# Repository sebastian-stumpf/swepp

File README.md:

# swepp

## Attention

I'm a hobbyist/amateur at best. So there may be things that aren't optimized. That being said I've had the files
in the `gerbers/` directory manufactured at JLC with 1.6mm thickness and they work just fine with my fork of the qmk repository
directory. So if you decide to use this, then please be advised that I'm not providing any sort of liability and you should
exercise some caution.

## Case

There are three options for the case: The first one is a simple FR4 stack. You'll need some M2 spacers and screws to fix it all
together. Plates and bottoms are reversible. The second option is a simple tray case. You'll need M2 heat inserts and screws to
fix the plate to the bottom. If you don't like the 3d printed plate you can also use the FR4 plate with spacers in this case.
The final option is a massive gasket mounted case that hides the switches.

## BOM

| Quantity   | Item                               | Comment                       |
| ---------  | ---------------------------------- | ----------------------------- |
| 2          | Helios or Liatris Controller       |                               |
| 2          | IC-Sockets+Pins for MCU            | Optional but recommended      |
| 2          | TRRS Sockets                       |                               |
| 2          | SKHLLBA010 buttons                 |                               |
| 34         | MX Hotswap Sockets                 |                               |
| 34         | MX Switches + Keycaps              |                               |
| 12         | M2 Screws                          | (countersunk for gasket case) |
| 12         | M2 heat inserts                    | Only for the 3d printed cases |

## Firmware

See [my fork](https://github.com/sebastian-stumpf/qmk_firmware/tree/sepp/keyboards/swepp) of the qmk repository. Nothing special here.
You can just copy the code over to your own repository and adjust the keymap.

## Feedback

I'm always happy to hear your opinions about this and if you decide to build this board then please do send me a picture of it.

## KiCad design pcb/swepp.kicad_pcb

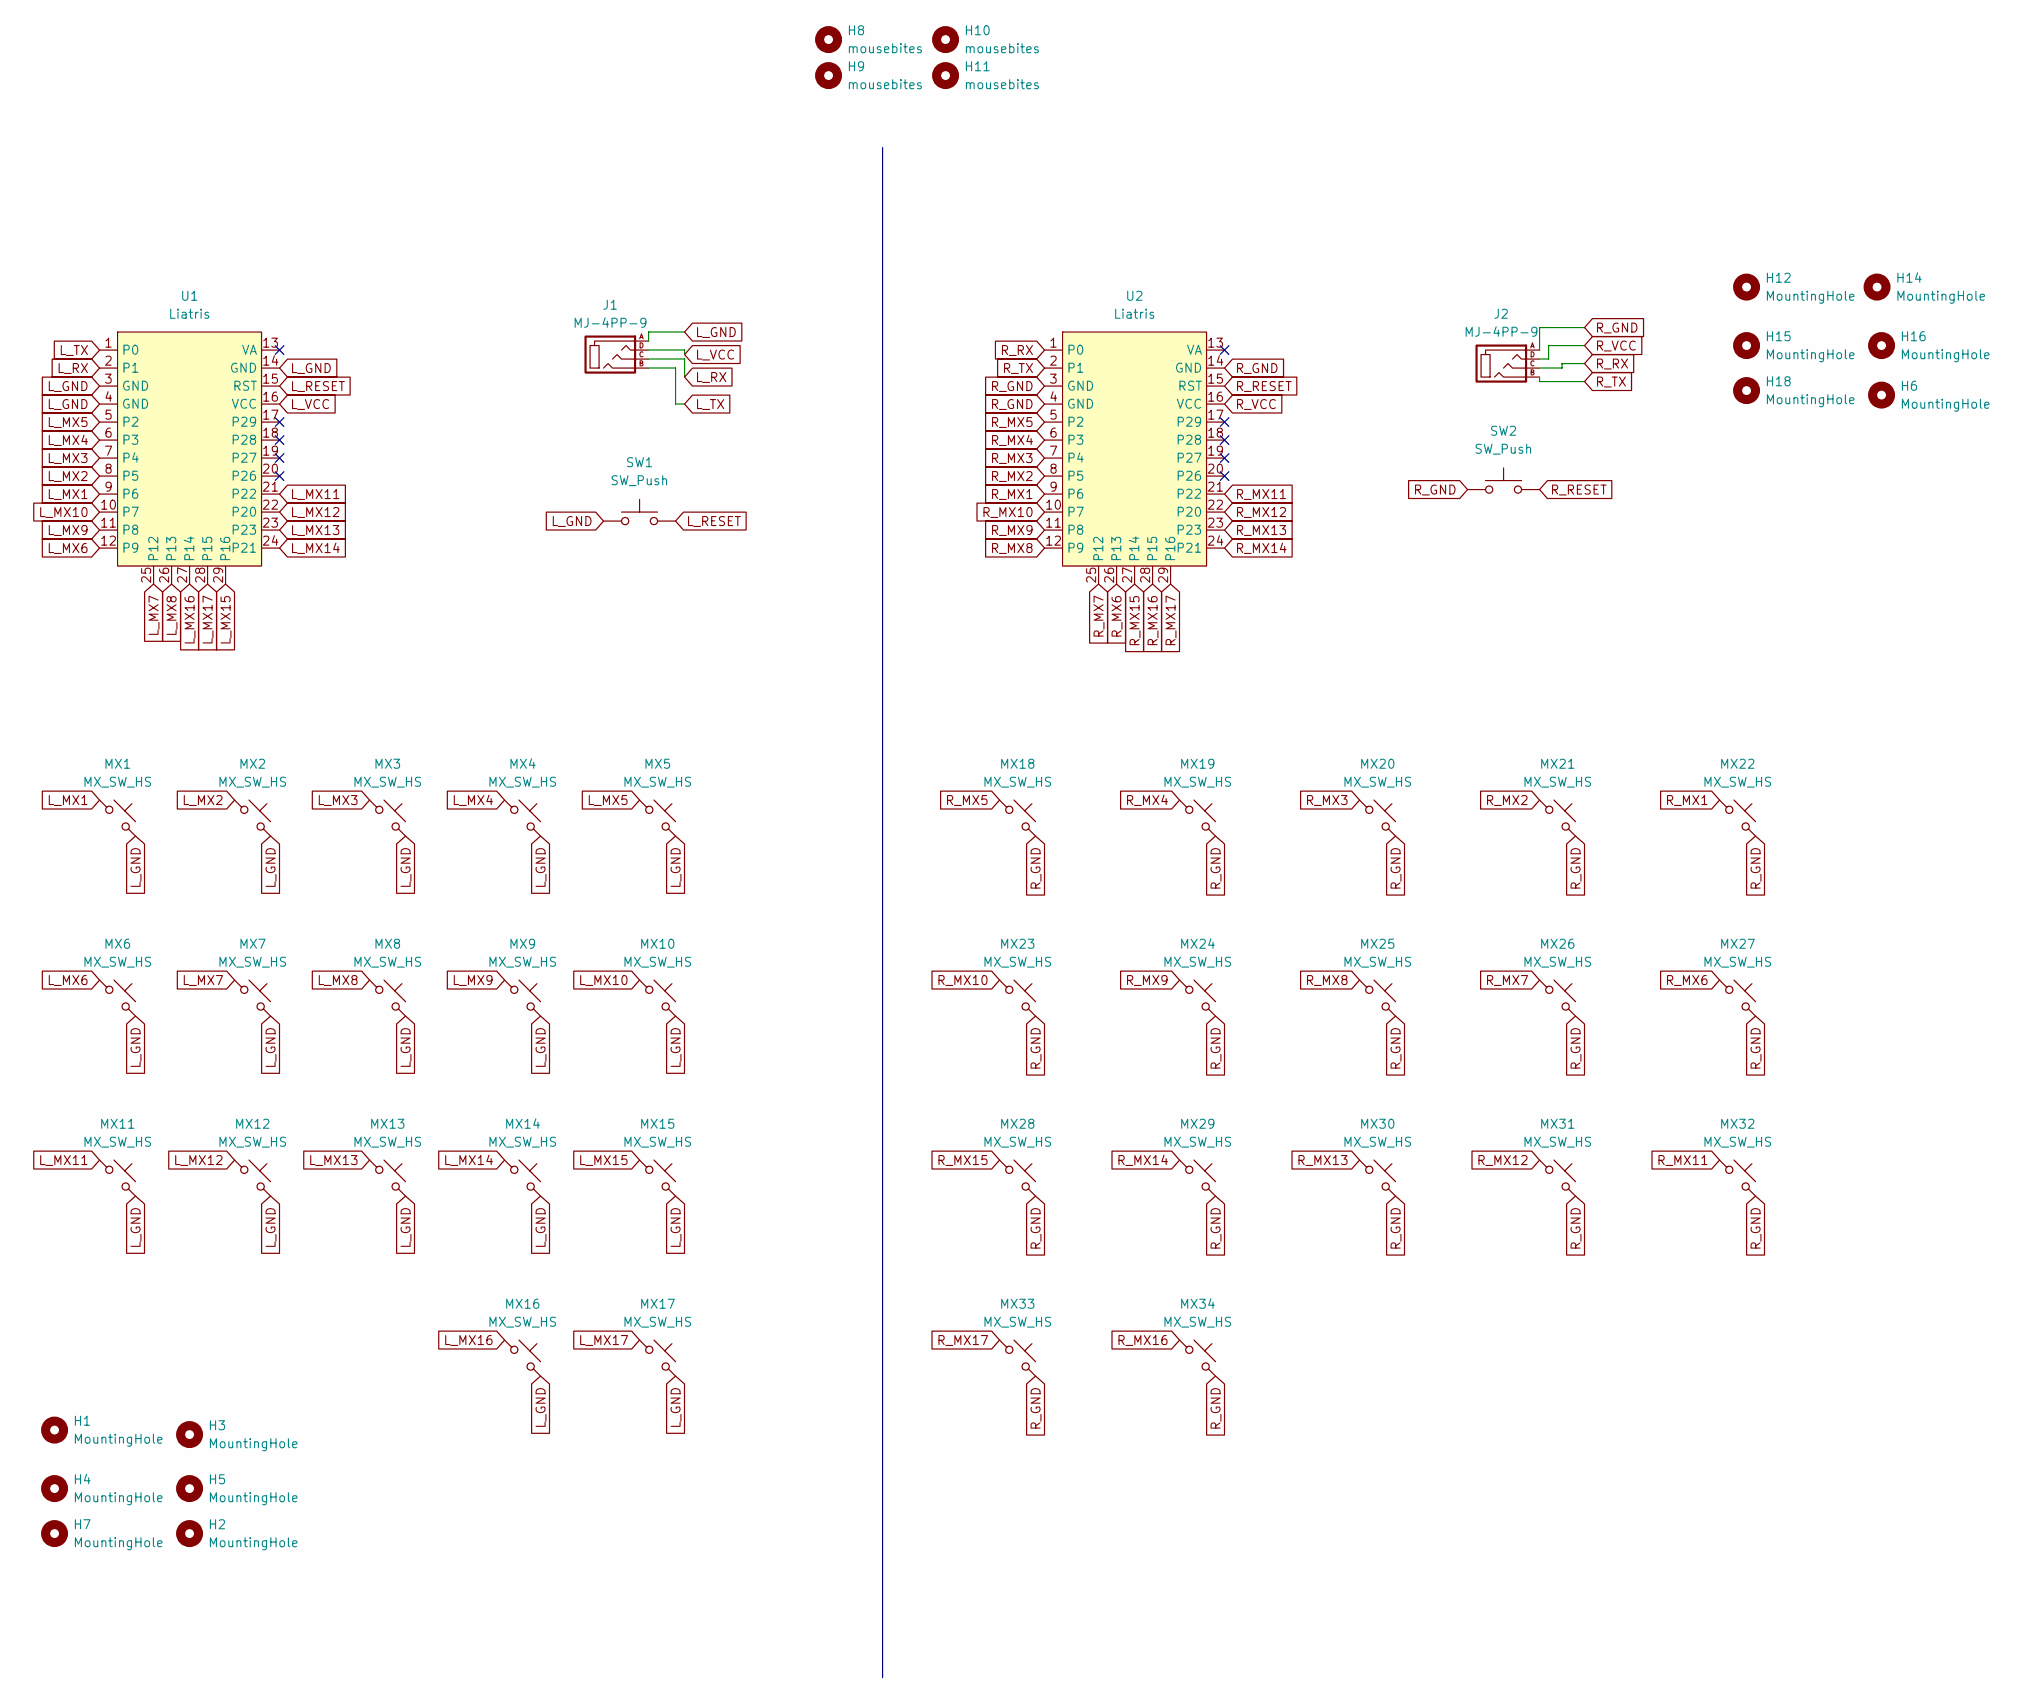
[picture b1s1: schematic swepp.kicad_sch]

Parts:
H1, H2, H3, H4, H5, H6, H7, H12, H14, H15, H16, H18: MountingHole; MountingHole_2.2mm_M2_DIN965
H8, H9, H10, H11: mousebites; breakaway-mousebites
J1, J2: MJ-4PP-9
MX1, MX2, MX3, MX4, MX5, MX6, MX7, MX8, MX9, MX10, MX11, MX12, MX13, MX14, MX15, MX16, MX17, MX18, MX19, MX20, MX21, MX22, MX23, MX24, MX25, MX26, MX27, MX28, MX29, MX30, MX31, MX32, MX33, MX34: MX_SW_HS; SW_MX_HS_1u
SW1, SW2: SW_Push; top_reset
U1, U2: Liatris; Liatris_AH_USBdn

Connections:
L_GND: J1.A, MX1.2, MX2.2, MX3.2, MX4.2, MX5.2, MX6.2, MX7.2, MX8.2, MX9.2, MX10.2, MX11.2, MX12.2, MX13.2, MX14.2, MX15.2, MX16.2, MX17.2, SW1.1, U1.3 (GND), U1.4 (GND), U1.14 (GND)
L_MX1: MX1.1, U1.9 (P6)
L_MX2: MX2.1, U1.8 (P5)
L_MX3: MX3.1, U1.7 (P4)
L_MX4: MX4.1, U1.6 (P3)
L_MX5: MX5.1, U1.5 (P2)
L_MX6: MX6.1, U1.12 (P9)
L_MX7: MX7.1, U1.25 (P12)
L_MX8: MX8.1, U1.26 (P13)
L_MX9: MX9.1, U1.11 (P8)
L_MX10: MX10.1, U1.10 (P7)
L_MX11: MX11.1, U1.21 (P22)
L_MX12: MX12.1, U1.22 (P20)
L_MX13: MX13.1, U1.23
L_MX14: MX14.1, U1.24 (P21)
L_MX15: MX15.1, U1.29 (P16)
L_MX16: MX16.1, U1.27 (P14)
L_MX17: MX17.1, U1.28 (P15)
L_RESET: SW1.2, U1.15 (RST)
L_RX: J1.C, U1.2 (P1)
L_TX: J1.B, U1.1 (P0)
L_VCC: J1.D, U1.16 (VCC)
R_GND: J2.A, MX18.2, MX19.2, MX20.2, MX21.2, MX22.2, MX23.2, MX24.2, MX25.2, MX26.2, MX27.2, MX28.2, MX29.2, MX30.2, MX31.2, MX32.2, MX33.2, MX34.2, SW2.1, U2.3 (GND), U2.4 (GND), U2.14 (GND)
R_MX1: MX22.1, U2.9 (P6)
R_MX2: MX21.1, U2.8 (P5)
R_MX3: MX20.1, U2.7 (P4)
R_MX4: MX19.1, U2.6 (P3)
R_MX5: MX18.1, U2.5 (P2)
R_MX6: MX27.1, U2.26 (P13)
R_MX7: MX26.1, U2.25 (P12)
R_MX8: MX25.1, U2.12 (P9)
R_MX9: MX24.1, U2.11 (P8)
R_MX10: MX23.1, U2.10 (P7)
R_MX11: MX32.1, U2.21 (P22)
R_MX12: MX31.1, U2.22 (P20)
R_MX13: MX30.1, U2.23
R_MX14: MX29.1, U2.24 (P21)
R_MX15: MX28.1, U2.27 (P14)
R_MX16: MX34.1, U2.28 (P15)
R_MX17: MX33.1, U2.29 (P16)
R_RESET: SW2.2, U2.15 (RST)
R_RX: J2.C, U2.1 (P0)
R_TX: J2.B, U2.2 (P1)
R_VCC: J2.D, U2.16 (VCC)

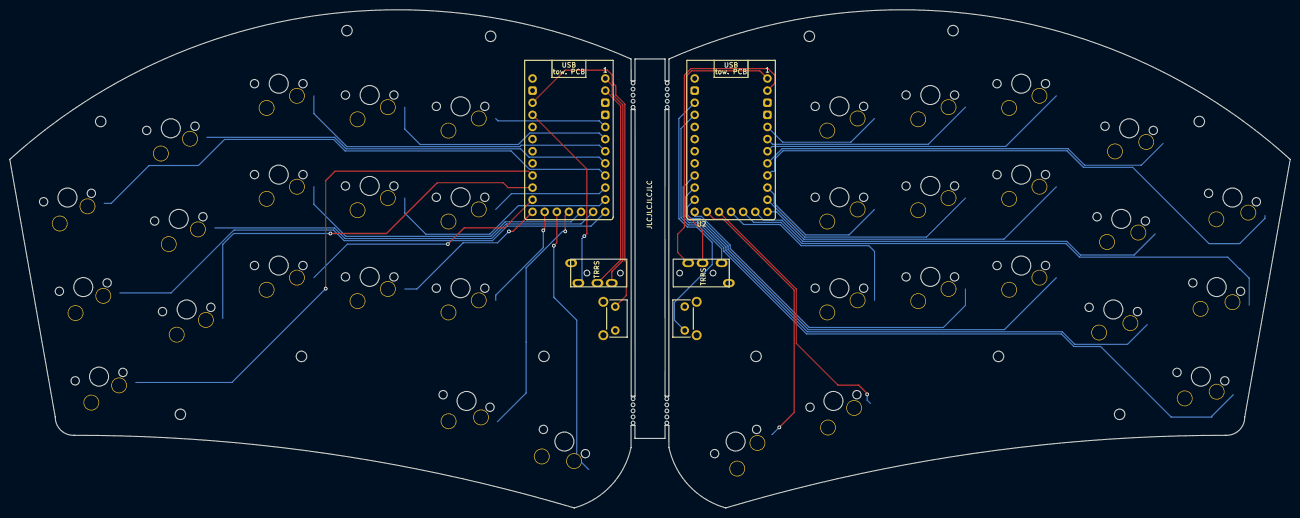
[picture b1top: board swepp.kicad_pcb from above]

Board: 2 copper layers, 268.3 x 104.4 mm, 56 parts (0 on the bottom side), 44 nets.

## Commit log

2023-11-14 added readme/license
2023-11-14 added missing libs
